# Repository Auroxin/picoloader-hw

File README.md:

# PicoLoader — hardware

Open-hardware design files for **PicoLoader**, an RP2040-based modchip for the Nintendo
GameCube. The main board carries the RP2040, the SPI flash and a USB-C port, and is wired to
the console through a 30-pin **solderless flex** that taps the DVD-drive flex connector
(footprint symbol `GamecubeConnectors:DVDFlexCN`). No soldering is required for installation.

The **16 MB** version ships with the PicoLoader firmware and the `swiss_r2092` boot payloads
preloaded, so no IPL file is needed on the SD card — copy your game files and play.

All projects are **KiCad 10** (PCB format `20260206`, schematic format `20260306`).

## Versions at a glance

| Folder | Revision | Status | SPI flash | Board size | Footprints |
| --- | --- | --- | --- | --- | --- |
| [`hw/v1.1/`](hw/v1.1) | v1.1 | **Discontinued** — kept for design history | ZD25WQ16CEIGR · 2 MB · USON-8 3×2 mm | 27.21 × 36.04 mm | 37 |
| [`hw/v1.1A/`](hw/v1.1A) | v1.1A | **In production** | ZD25WQ16DEIGR · 2 MB · USON-8 3×2 mm | 27.21 × 36.04 mm | 39 |
| [`hw/v1.2A/`](hw/v1.2A) | v1.2A | **In production** | ZD25WQ128CEIGR · 16 MB · WSON-8 6×5 mm | 27.21 × 36.04 mm | 39 |
| [`hw/flex/`](hw/flex) | flex | **In production** | — | 98.46 × 61.01 mm | 2 |

v1.1 is retired and is published only for reference. The current production board is
**v1.2A**; **v1.1A** is the previous 2 MB revision and remains available as the lower-cost
option.

## What the 16 MB version adds

v1.2A is an evolution of v1.1A. The flash footprint moves from USON-8 3×2 mm to WSON-8
6×5 mm so that a 16 MB part can replace the 2 MB one, which brings:

| | **16 MB (v1.2A)** | **2 MB (v1.1A)** |
| --- | --- | --- |
| Onboard flash | 16 MB SPI flash | 2 MB SPI flash |
| PicoLoader firmware | Preloaded | Supported, has to be flashed |
| Swiss boot payload | `swiss_r2092` preloaded | Usually requires separate setup |
| SD card IPL file | Not required | Usually needs an IPL file on the SD card |
| After installation | Copy game files and play | Extra setup steps are often needed |
| Convenience | Plug-and-play | Requires a bit more work |

Both revisions keep the same PCB outline, the same RP2040, USB-C and 30-pin FFC interface,
so a 2 MB board can be swapped for a 16 MB one in an existing installation.

## Gallery

<p align="center"><em>v1.2A (16 MB) · v1.1A (2 MB) · solderless flex</em></p>

## Where to buy

Pre-built units fund the continued development of this hardware and its firmware:

* **v1.1A (2 MB)** — <https://www.aliexpress.com/item/1005012408459349.html>
* **v1.2A (16 MB)** — <https://www.aliexpress.com/item/1005013055513154.html>

If you would rather build your own from these files, that is exactly what the licence is
for — a star on the repository or a note about your build is always appreciated.

## Fabrication files

Ready-to-order Gerber / drill packages, the BOM and the top-side assembly drawing are
published per revision:

* [PicoLoader **v1.2A** (16 MB)](https://github.com/Auroxin/picoloader-hw/releases/tag/v1.2A) — Gerber + drill, BOM, assembly drawing
* [PicoLoader **v1.1A** (2 MB)](https://github.com/Auroxin/picoloader-hw/releases/tag/v1.1A) — Gerber + drill, BOM, assembly drawing

The design sources are in [`hw/`](hw); every fabrication file above is generated from them,
so you can always re-plot from the project instead of trusting an archive.

## 3D-printed parts

A solderless installation also needs the printed bracket that holds the board. The parts live
in [`3d-print/`](3d-print):

| File | Format | Purpose |
| --- | --- | --- |
| `Drive_PlugV1.1.stl` | STL | Drive-side plug, used when the console runs without a disc drive |
| `Fold_KeyV1.2.stl` | STL | Folding key that creases the flex cable at the correct position |
| `picoloader-pcb-plug-20260901.step` | STEP | Mounting bracket that holds the main board (rev 1.2A) |

## Component summary (main board)

| Designator | Part | Package |
| --- | --- | --- |
| U3 | RP2040 | QFN-56 7×7 mm P0.4 mm |
| FLASH1 | ZD25WQ128CEIGR (16 MB, v1.2A) · ZD25WQ16DEIGR (2 MB, v1.1A) · ZD25WQ16CEIGR (2 MB, v1.1) | WSON-8 6×5 mm (v1.2A) · USON-8 3×2 mm (v1.1, v1.1A) |
| U1 | AP2112K-3.3TRG1 LDO | SOT-23-5 |
| Y1 | 12 MHz crystal | SMD 3225 |
| J1 | 30-pin 0.5 mm FFC | Hirose FH12-30S-0.5SH-1 |
| USB2 | USB-C receptacle | HRO TYPE-C-31-M-12 |
| J2, RSW1 | Tactile switch | Panasonic TSA343G00-250J2 |
| D1, D3 | 1N5819WS Schottky | SOD-323 |
| D2 | Indicator LED | 0603 |
| TP3–TP5 | Test points | 1.0 mm pad |

The board is powered from USB-C through the LDO and carries 23 discrete resistors and
capacitors (0402 / 0603).

The schematic symbol block also lists **W25Q256JVEIQ** (32 MB) as an alternative QSPI part
for the same footprint, in case a larger flash is wanted.

## Repository layout

```
.
├── LICENSE                  GPL-2.0
├── NOTICE.md                upstream attribution and file-level provenance
├── extras/                  PCB renders and product graphics
├── 3d-print/                STL / STEP parts for a solderless install
└── hw/
    ├── v1.1/                discontinued — picoloader.kicad_{pro,sch,pcb}
    │   ├── fp-lib-table     project footprint table (${KIPRJMOD})
    │   ├── sym-lib-table    project symbol table (${KIPRJMOD})
    │   ├── Library.pretty   project footprints
    │   └── packages3D/      3D models referenced by the PCB
    ├── v1.1A/               same structure
    ├── v1.2A/               same structure
    └── flex/                Flex.kicad_{pro,sch,pcb}
        ├── fp-lib-table
        ├── sym-lib-table
        ├── GamecubeConnectors.kicad_sym
        └── Library.pretty
```

Every project folder is **self-contained**: `fp-lib-table` and `sym-lib-table` resolve
through `${KIPRJMOD}`, and `packages3D/` only contains the models the PCB actually
references. Clone the repository and open the `.kicad_pro` file of the revision you want; no
extra library installation is needed. Each folder also has a short `README.md` with the
revision-specific details.

## Working with the projects

* Open the `.kicad_pro` file directly in KiCad 10.0 or newer. Older KiCad versions will
  refuse to open the schematic and PCB because of the file format version.
* Footprints from `Library.pretty` are embedded in the PCB files as well, so the boards
  render even if the library is not loaded; the library tables are provided so that
  "update footprint from library" works.
* Symbol libraries `MCU_RaspberryPi_RP2040`, `Type-C` and `W25Q256JVEIQ_TR` are third-party
  libraries and are **not redistributed** here. Each `.kicad_sch` carries a full
  `lib_symbols` cache, so the schematics display and plot correctly; only
  "update symbol from library" will report the missing libraries.
* `Library.kicad_sym` in the board projects is intentionally an empty stub — it only keeps
  the project symbol table consistent with the original design environment.
* Fabrication outputs are not tracked in the repository — each revision has a
  [release](https://github.com/Auroxin/picoloader-hw/releases) with the Gerber / drill
  package, the BOM and the assembly drawing. Re-plot from the project if you want a fresh
  set.

## Acknowledgements

This project exists because of the **PicoLoader open-source community**. Thank you all.

* **makeo** — for creating PicoLoader, for writing the installation documentation, and above
  all for releasing the design under GPL-2.0 so that others can study it and build on it:
  <https://github.com/makeo/PicoLoader>
* **silversteel** — for the flex PCB and the printed mounts that make the solderless install
  possible
* **the PicoLoader community** — for the wiki and installation guides, the boot payload
  converter, the support on Discord, and for testing every revision on real consoles
* **emukidid, Extrems and the swiss-gc contributors** — for Swiss, the software these boards
  boot
* **TeamOffBroadway** — for the idea of intercepting the drive signals with a flex PCB
* **novenary (9ary)** — for gekkoboot

This repository only adds the v1.1A / v1.2A board revisions and the parts needed to build
them; the concept, the flex and the mounts are the work of the people above. If you build one
of these, consider contributing your findings back to the upstream project as well.

## Third-party assets

`packages3D/` contains vendor STEP models (HRO, Hirose, Winbond, Panasonic, RP2040 QFN and
generic passive footprints). They are included purely for mechanical reference and remain
the property of their respective manufacturers.

Footprints in `Library.pretty` that were derived from the official KiCad libraries stay under
the KiCad library licence (CC-BY-SA 4.0); KiCad's design exception means the boards built
from them are not affected by that licence.

## License

This repository is distributed under the **GNU General Public License v2.0 (GPL-2.0)**, the
same licence as the upstream [PicoLoader](https://github.com/makeo/PicoLoader) project it
derives from. See [LICENSE](LICENSE) for the full text and [NOTICE.md](NOTICE.md) for exactly
which files come from upstream.

In practice:

* you may build, modify and **sell hardware** made from these files, including commercially —
  the GPL does not restrict manufacturing or selling products;
* if you redistribute the design files, the modified sources must stay under GPL-2.0, keep
  this notice and the licence, and remain available to whoever receives the design;
* the design is provided **as is**, without any warranty; building and using it is at your
  own risk.

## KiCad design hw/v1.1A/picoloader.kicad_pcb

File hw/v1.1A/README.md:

# picoloader v1.1A — in production (2 MB)

The 2 MB revision, still sold alongside v1.2A.

* 27.21 × 36.04 mm, 39 footprints
* SPI flash `ZD25WQ16DEIGR` (2 MB), USON-8 3×2 mm
* footprints migrated to the standard KiCad libraries, silkscreen artwork added

PicoLoader firmware is supported but has to be flashed, and Swiss usually needs a separate
setup step. See [v1.2A](../v1.2A) for the 16 MB version that ships preloaded.

Open `picoloader.kicad_pro` with KiCad 10 or newer.

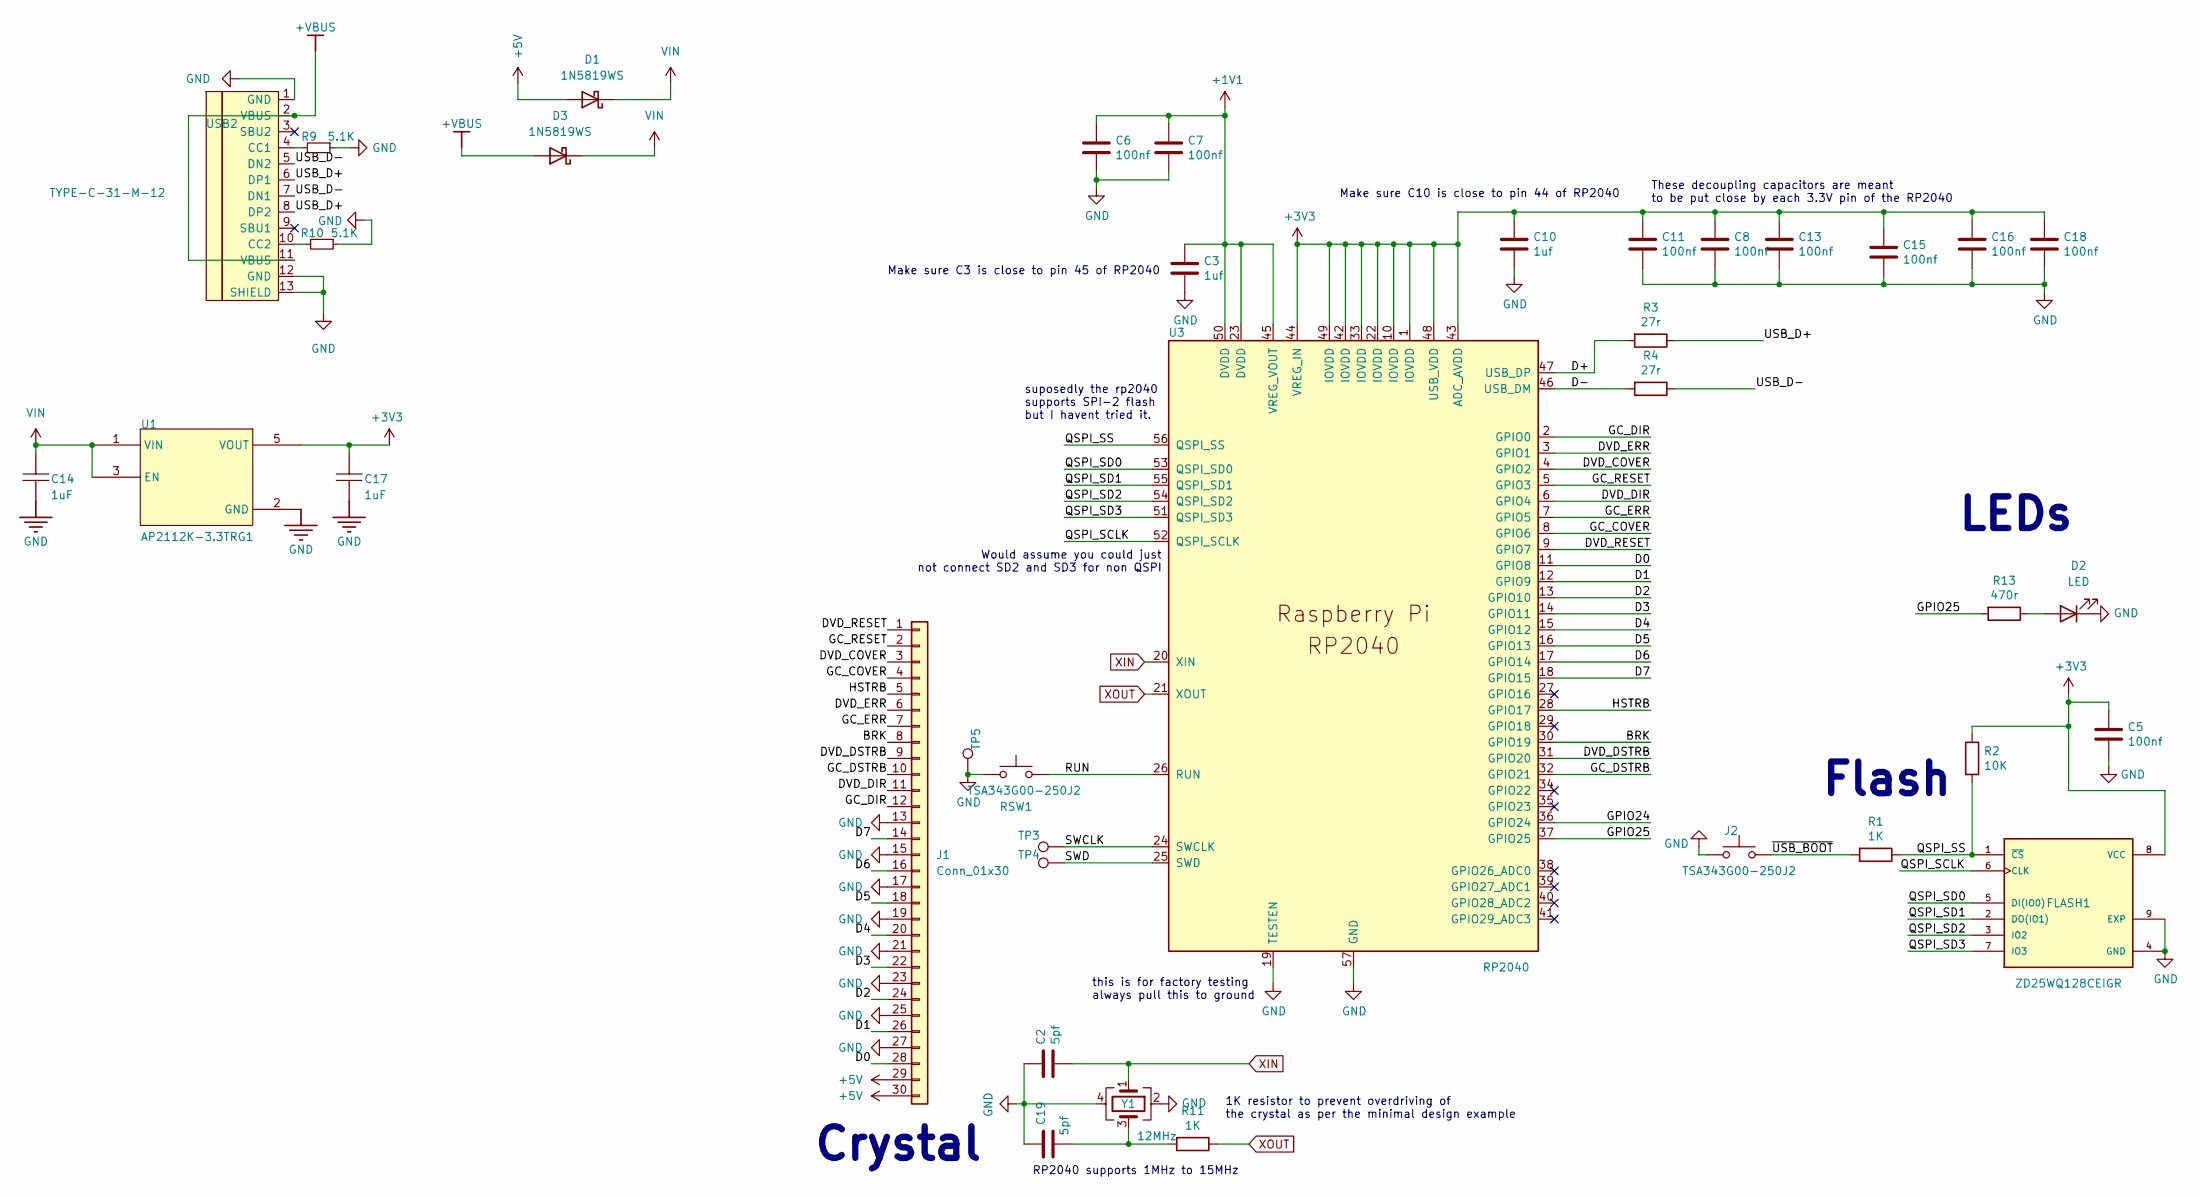
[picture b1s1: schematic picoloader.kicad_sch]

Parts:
C2, C19: 5pf; C_0402_1005Metric
C3, C10: 1uf; C_0603_1608Metric
C5, C6, C7, C8, C11, C13, C15, C16, C18: 100nf; C_0402_1005Metric
C14, C17: 1uF; C_0603_1608Metric; TOLERANCE 10%; VOLTAGE RATING 25V; MANUFACTURER PART NUMBER C1005X5R1E105K050BC
D1, D3: 1N5819WS; D_SOD-323
D2: LED; LED_0603_1608Metric
FLASH1: ZD25WQ128CEIGR; Winbond_USON-8-1EP_3x2mm_P0.5mm_EP0.2x1.6mm
J1: Conn_01x30; Hirose_FH12-30S-0.5SH_1x30-1MP_P0.50mm_Horizontal
J2: TSA343G00-250J2; SW_Push_SPST_NO_Alps_SKRK
R1, R11: 1K; R_0402_1005Metric
R2: 10K; R_0402_1005Metric
R3, R4: 27r; R_0402_1005Metric
R9, R10: 5.1K; R_0402_1005Metric
R13: 470r; R_0402_1005Metric
RSW1: TSA343G00-250J2; SW_Push_SPST_NO_Alps_SKRK
TP3, TP4, TP5: TestPoint; TestPoint_Pad_D1.0mm
U1: AP2112K-3.3TRG1; SOT-23-5; DROPOUT VOLTAGE 250mV; OUTPUT VOLTAGE 3.3V; MANUFACTURER PART NUMBER AP2112K-3.3TRG1
U3: RP2040; RP2040-QFN-56; LCSC C2040
USB2: TYPE-C-31-M-12; HRO-TYPE-C-31-M-12; LCSC C165948
Y1: 12MHz; Crystal_SMD_3225-4Pin_3.2x2.5mm

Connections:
+1V1: C3.1, C6.1, C7.1, U3.23 (DVDD), U3.45 (VREG_VOUT), U3.50 (DVDD)
+3V3: C5.1, C8.1, C10.1, C11.1, C13.1, C15.1, C16.1, C17.2, C18.1, FLASH1.8 (VCC), R2.1, U1.5 (VOUT), U3.1 (IOVDD), U3.10 (IOVDD), U3.22 (IOVDD), U3.33 (IOVDD), U3.42 (IOVDD), U3.43 (ADC_AVDD), U3.44 (VREG_IN), U3.48 (USB_VDD), U3.49 (IOVDD)
+5V: D1.2 (A), J1.29, J1.30
+VBUS: D3.2 (A), USB2.2 (VBUS), USB2.11 (VBUS)
/BRK: J1.8, U3.30 (GPIO19)
/D0: J1.28, U3.11 (GPIO8)
/D1: J1.26, U3.12 (GPIO9)
/D2: J1.24, U3.13 (GPIO10)
/D3: J1.22, U3.14 (GPIO11)
/D4: J1.20, U3.15 (GPIO12)
/D5: J1.18, U3.16 (GPIO13)
/D6: J1.16, U3.17 (GPIO14)
/D7: J1.14, U3.18 (GPIO15)
/D+: R3.2, U3.47 (USB_DP)
/D-: R4.2, U3.46 (USB_DM)
/DVD_COVER: J1.3, U3.4 (GPIO2)
/DVD_DIR: J1.11, U3.6 (GPIO4)
/DVD_DSTRB: J1.9, U3.31 (GPIO20)
/DVD_ERR: J1.6, U3.3 (GPIO1)
/DVD_RESET: J1.1, U3.9 (GPIO7)
/GC_COVER: J1.4, U3.8 (GPIO6)
/GC_DIR: J1.12, U3.2 (GPIO0)
/GC_DSTRB: J1.10, U3.32 (GPIO21)
/GC_ERR: J1.7, U3.7 (GPIO5)
/GC_RESET: J1.2, U3.5 (GPIO3)
/GPIO24: U3.36 (GPIO24)
/GPIO25: R13.2, U3.37 (GPIO25)
/HSTRB: J1.5, U3.28 (GPIO17)
/QSPI_SCLK: FLASH1.6 (CLK), U3.52 (QSPI_SCLK)
/QSPI_SD0: FLASH1.5 (DI(IO0)), U3.53 (QSPI_SD0)
/QSPI_SD1: FLASH1.2 (DO(IO1)), U3.55 (QSPI_SD1)
/QSPI_SD2: FLASH1.3 (IO2), U3.54 (QSPI_SD2)
/QSPI_SD3: FLASH1.7 (IO3), U3.51 (QSPI_SD3)
/QSPI_SS: FLASH1.1 (~CS), R1.1, R2.2, U3.56 (QSPI_SS)
/RUN: RSW1.2, U3.26 (RUN)
/SWCLK: TP3.1 (1_1), U3.24 (SWCLK)
/SWD: TP4.1 (1_1), U3.25 (SWD)
/USB_D+: R3.1, USB2.6 (DP1), USB2.8 (DP2)
/USB_D-: R4.1, USB2.5 (DN2), USB2.7 (DN1)
/~USB_BOOT: J2.1, R1.2
GND: C2.1, C3.2, C5.2, C6.2, C7.2, C8.2, C10.2, C11.2, C13.2, C14.1, C15.2, C16.2, C17.1, C18.2, C19.1, D2.1 (K), FLASH1.4 (GND), FLASH1.9 (EXP), J1.13, J1.15, J1.17, J1.19, J1.21, J1.23, J1.25, J1.27, J1.MP, J2.2, R9.1, R10.1, RSW1.1, TP5.1 (1_1), U1.2 (GND), U3.19 (TESTEN), U3.57 (GND), USB2.1 (GND), USB2.12 (GND), USB2.13 (SHIELD), Y1.2, Y1.4
unnamed: C19.2, R11.2, Y1.3
unnamed: D2.2 (A), R13.1
unnamed: R9.2, USB2.4 (CC1)
unnamed: R10.2, USB2.10 (CC2)
VIN: C14.2, D1.1 (K), D3.1 (K), U1.1 (VIN), U1.3 (EN)
XIN: C2.2, U3.20 (XIN), Y1.1
XOUT: R11.1, U3.21 (XOUT)

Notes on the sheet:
These decoupling capacitors are meant to be put close by each 3.3V pin of the RP2040
this is for factory testing always pull this to ground
suposedly the rp2040 supports SPI-2 flash but I havent tried it.
1K resistor to prevent overdriving of the crystal as per the minimal design example
LEDs
Crystal
Flash
RP2040 supports 1MHz to 15MHz
Make sure C3 is close to pin 45 of RP2040
Make sure C10 is close to pin 44 of RP2040
Would assume you could just not connect SD2 and SD3 for non QSPI

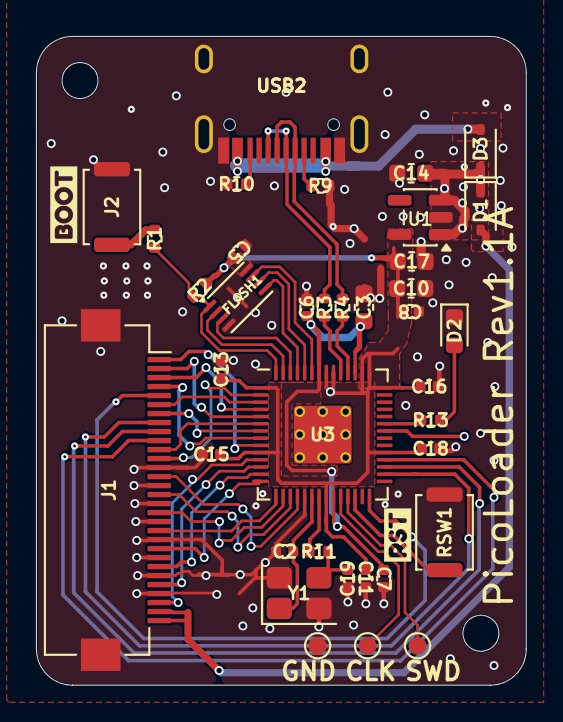
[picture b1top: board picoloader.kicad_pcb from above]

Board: 2 copper layers, 27.2 x 36.0 mm, 39 parts (0 on the bottom side), 47 nets.

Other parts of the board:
kibuzzard-6A867A8B: G***; kibuzzard-6A867A8B
kibuzzard-6A867A9B: G***; kibuzzard-6A867A9B
